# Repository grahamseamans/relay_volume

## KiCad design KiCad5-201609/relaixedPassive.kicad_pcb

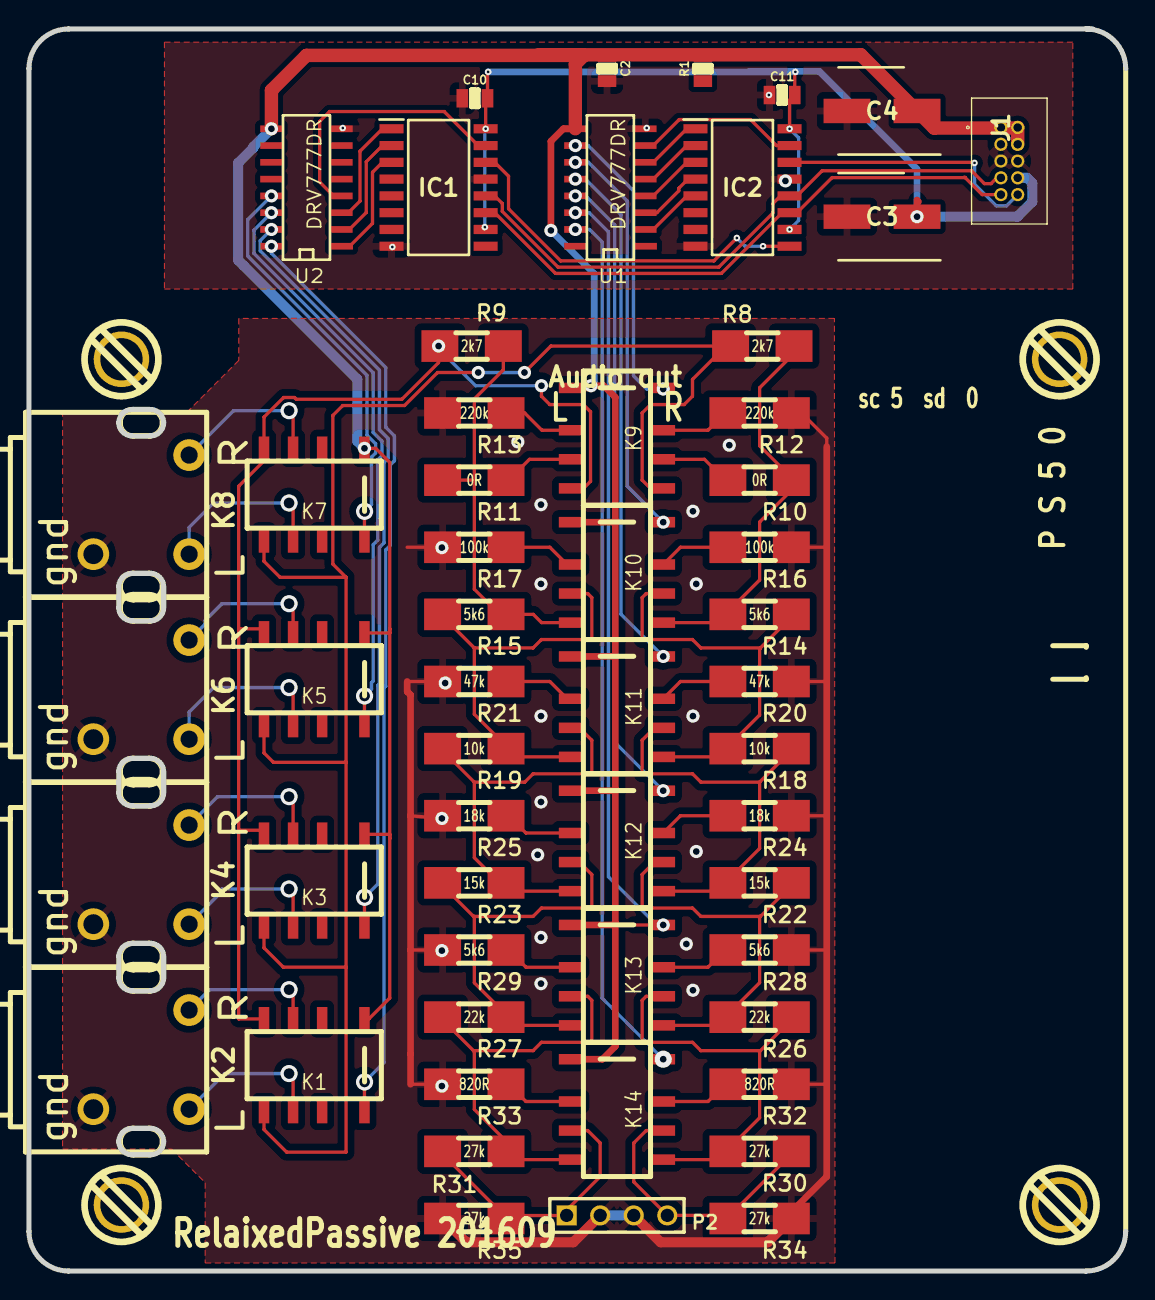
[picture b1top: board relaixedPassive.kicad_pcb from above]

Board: 2 copper layers, 83.0 x 94.0 mm, 58 parts (0 on the bottom side), 64 nets.

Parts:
1PIN, 1PIN#2, 1PIN#3, 1PIN#4: P***; screw-3mm
C2: 10uF; R0805
C3, C4: VZL221M1CTR-0607; CAPAE660X800N
C10, C11: 0.1uf; R0805
IC1, IC2: SN74HC595NSR; SOIC127P780X200-16N
J1: TFM-105-01-F-D; TFM-105-XX-YYY-D
K1, K3, K5, K7: RELAY_G6K_AB; G6K-2F-Y
K2, K4, K6, K8: CINCH-DUAL; switchcraft-dualcinch
K9, K10, K11, K12, K13, K14: RELAY_G6K; G6K-2F-Y
P2: audioOut; PIN_ARRAY_4x1
R1: 1k; R0805
R8, R9: 2k7; MMB0207-1210
R10, R11: 0R; MMB0207-1210
R12, R13: 220k; MMB0207-1210
R14, R15, R28, R29: 5k6; MMB0207-1210
R16, R17: 100k; MMB0207-1210
R18, R19: 10k; MMB0207-1210
R20, R21: 47k; MMB0207-1210
R22, R23: 15k; MMB0207-1210
R24, R25: 18k; MMB0207-1210
R26, R27: 22k; MMB0207-1210
R30, R31, R34, R35: 27k; MMB0207-1210
R32, R33: 820R; MMB0207-1210
U1, U2: DRV777DR; SO16E

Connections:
+3.3V: C3.1, C10.2, C11.2, IC1.10 (~SRCLR), IC1.16 (VCC), IC2.10 (~SRCLR), IC2.16 (VCC), J1.8
+5V: C2.1, C4.1, J1.1, J1.2, J1.4, K1.1, K3.1, K5.1, K7.1, K9.1, K10.1, K11.1, K12.1, K13.1, K14.1, R1.2, U1.9 (COM), U2.9 (COM)
AGND: K2.3 (GL), K4.3 (GL), K6.3 (GL), K8.3 (GL), P2.2, P2.3, R12.1, R13.1, R16.1, R17.1, R20.1, R21.1, R24.1, R25.1, R28.1, R29.1, R32.1, R33.1, R34.2, R35.2
CH1: K1.8, U2.16 (O1)
CH2: K3.8, U2.15 (O2)
CH3: K5.8, U2.14 (O3)
CH4: K7.8, U2.13 (O4)
DGND: C2.2, C3.2, C4.2, C10.1, C11.1, IC1.8 (GND), IC1.13 (~OE), IC2.8 (GND), IC2.13 (~OE), J1.3, J1.5, J1.6, U1.8 (GND), U2.8 (GND)
unnamed: IC1.14 (SER), IC2.9 (QH')
unnamed: K1.4, K3.4, K5.4, K7.4, K9.4, R9.2
unnamed: K1.5, K3.5, K5.5, K7.5, K9.5, R8.2
unnamed: K1.6, K2.2 (L)
unnamed: K1.3, K2.1 (R)
unnamed: K3.6, K4.2 (L)
unnamed: K3.3, K4.1 (R)
unnamed: K5.6, K6.2 (L)
unnamed: K5.3, K6.1 (R)
unnamed: K7.6, K8.2 (L)
unnamed: K7.3, K8.1 (R)
unnamed: K9.2, R13.2
unnamed: K9.3, R11.2
unnamed: K9.6, R10.2
unnamed: K9.7, R12.2
unnamed: K10.2, R17.2
unnamed: K10.3, K11.4, R15.1, R19.2
unnamed: K10.4, R9.1, R11.1, R15.2
unnamed: K10.5, R8.1, R10.1, R14.2
unnamed: K10.6, K11.5, R14.1, R18.2
unnamed: K10.7, R16.2
unnamed: K11.2, R21.2
unnamed: K11.3, K12.4, R19.1, R23.2
unnamed: K11.6, K12.5, R18.1, R22.2
unnamed: K11.7, R20.2
unnamed: K12.2, R25.2
unnamed: K12.3, K13.4, R23.1, R27.2
unnamed: K12.6, K13.5, R22.1, R26.2
unnamed: K12.7, R24.2
unnamed: K13.2, R29.2
unnamed: K13.3, K14.4, R27.1, R31.2
unnamed: K13.6, K14.5, R26.1, R30.2
unnamed: K13.7, R28.2
unnamed: K14.2, R33.2
unnamed: K14.7, R32.2
unnamed: K14.3, P2.1, R31.1, R35.1
unnamed: K14.6, P2.4, R30.1, R34.1
RCLK1: IC1.12 (RCLK), IC2.12 (RCLK), J1.7
SER1: IC2.14 (SER), J1.10
SRCLK1: IC1.11 (SRCLK), IC2.11 (SRCLK), J1.9
VL0: K9.8, U1.10 (O7)
VL0c: IC2.15 (QA), U1.7 (I7)
VL1: K10.8, U1.11 (O6)
VL1c: IC2.1 (QB), U1.6 (I6)
VL2: K11.8, U1.12 (O5)
VL2c: IC2.2 (QC), U1.5 (I5)
VL3: K12.8, U1.13 (O4)
VL3c: IC2.3 (QD), U1.4 (I4)
VL4: K13.8, U1.14 (O3)
VL4c: IC2.4 (QE), U1.3 (I3)
VL5: K14.8, U1.15 (O2)
VL5c: IC2.5 (QF), U1.2 (I2)
contCH1: IC1.15 (QA), U2.4 (I4)
contCH2: IC1.1 (QB), U2.3 (I3)
contCH3: IC1.2 (QC), U2.2 (I2)
contCH4: IC1.3 (QD), U2.1 (I1)

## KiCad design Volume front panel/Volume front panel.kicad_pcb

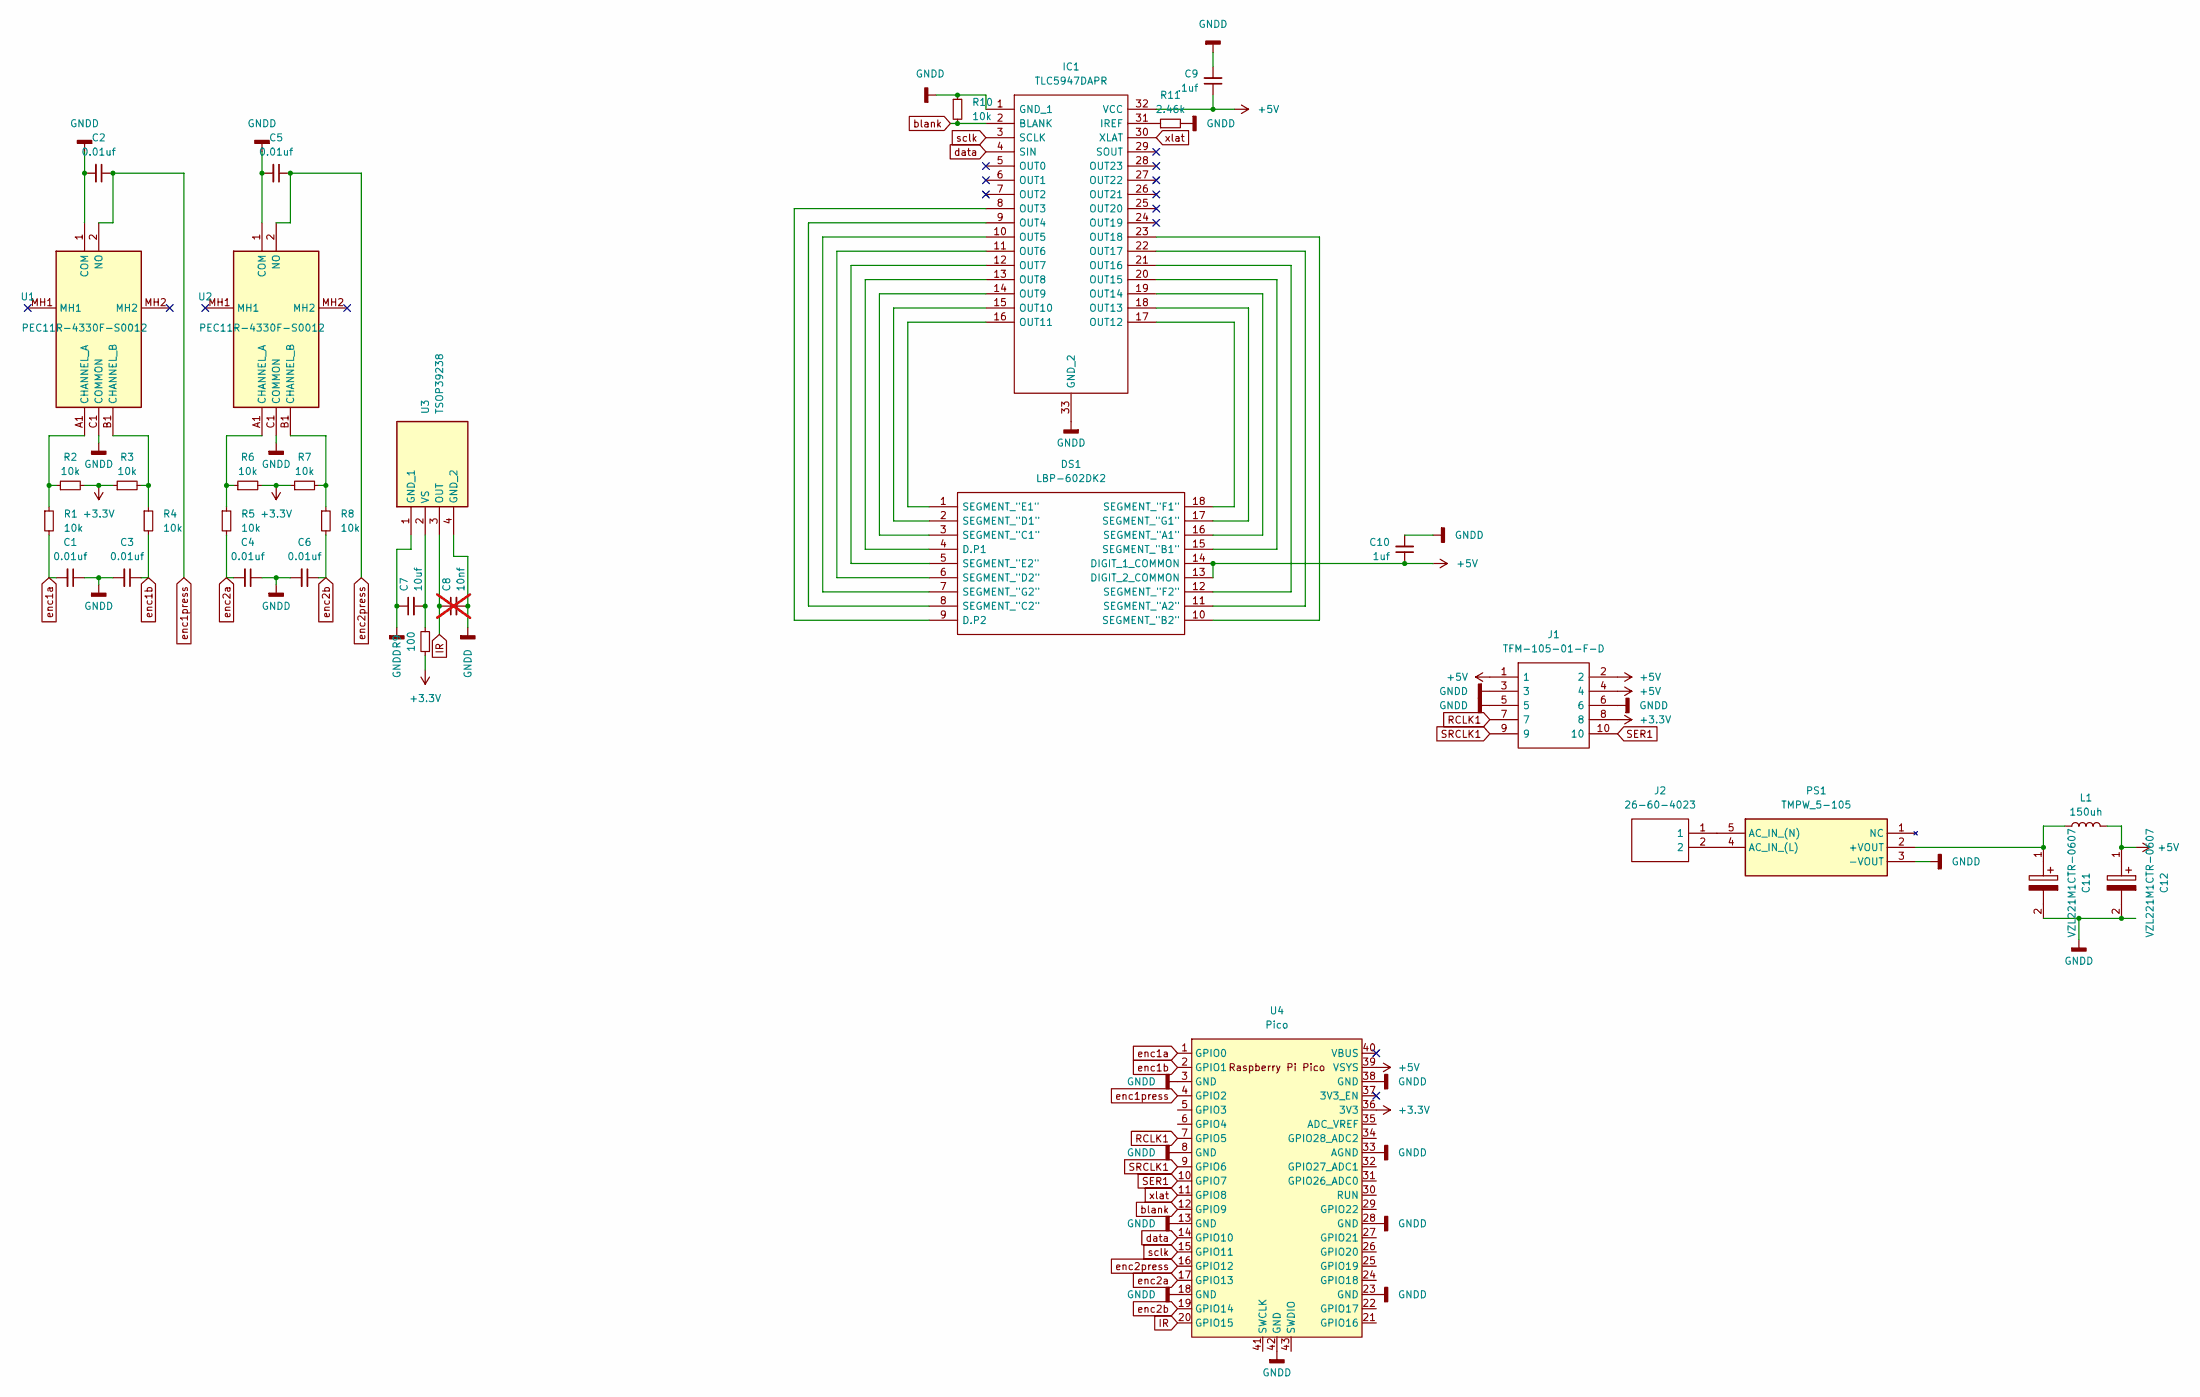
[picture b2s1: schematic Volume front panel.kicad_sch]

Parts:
C1, C2, C3, C4, C5, C6: 0.01uf; C_1206_3216Metric
C7: 10uf; C_1206_3216Metric
C8: 10nf; C_1206_3216Metric; not fitted
C9: .1uf; C_1206_3216Metric
C10: 1uf; C_1206_3216Metric
C11, C12: VZL221M1CTR-0607; CAPAE660X800N; Mouser Part Number 140-VZL221M1CTR-0607
DS1: LBP-602DK2; DIPS1524W50P254L2500H830Q18N; Mouser Part Number 755-LBP-602DK2
IC1: TLC5947DAPR; SOP65P810X120-33N; Mouser Part Number 595-TLC5947DAPR
J1: TFM-105-01-F-D; TFM-105-XX-YYY-D; Mouser Part Number 200-TFM10501FD
J2: 26-60-4023; 26604023; Mouser Part Number 538-26-60-4023
L1: 150uh; L_Coilcraft_XAL6060-XXX
PS1: TMPW_5-105; TMPW5112; Mouser Part Number 495-TMPW5-105
R1, R2, R3, R4, R5, R6, R7, R8, R10: 10k; R_1206_3216Metric
R9: 100; R_1206_3216Metric
R11: 2.46k; R_1206_3216Metric
U1, U2: PEC11R-4330F-S0012; PEC11R4330FS0012; Mouser Part Number 652-PEC11R4330FS0012
U3: TSOP39238; Mouser Part Number 78-TSOP39238
U4: Pico; RPi_Pico_SMD_TH

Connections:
+3.3V: J1.8, R2.2, R3.1, R6.2, R7.1, R9.1, U4.36 (3V3)
+5V: C9.1, C10.1, C12.1, DS1.13 (DIGIT_2_COMMON), DS1.14 (DIGIT_1_COMMON), IC1.32 (VCC), J1.1, J1.2, J1.4, L1.2, U4.39 (VSYS)
GNDD: C1.1, C2.2, C3.2, C4.1, C5.2, C6.2, C7.1, C8.2, C9.2, C10.2, C11.2, C12.2, IC1.1 (GND_1), IC1.33 (GND_2), J1.3, J1.5, J1.6, PS1.3 (-VOUT), R10.1, R11.2, U1.1 (COM), U1.C1 (COMMON), U2.1 (COM), U2.C1 (COMMON), U3.1 (GND_1), U3.4 (GND_2), U4.3 (GND), U4.8 (GND), U4.13 (GND), U4.18 (GND), U4.23 (GND), U4.28 (GND), U4.33 (AGND), U4.38 (GND), U4.42 (GND)
IR: C8.1, U3.3 (OUT), U4.20 (GPIO15)
unnamed: DS1.4 (D.P1), IC1.13 (OUT8)
unnamed: DS1.9 (D.P2), IC1.8 (OUT3)
unnamed: DS1.16 (SEGMENT_"A1"), IC1.19 (OUT14)
unnamed: DS1.11 (SEGMENT_"A2"), IC1.22 (OUT17)
unnamed: DS1.15 (SEGMENT_"B1"), IC1.20 (OUT15)
unnamed: DS1.10 (SEGMENT_"B2"), IC1.23 (OUT18)
unnamed: DS1.3 (SEGMENT_"C1"), IC1.14 (OUT9)
unnamed: DS1.8 (SEGMENT_"C2"), IC1.9 (OUT4)
unnamed: DS1.2 (SEGMENT_"D1"), IC1.15 (OUT10)
unnamed: DS1.6 (SEGMENT_"D2"), IC1.11 (OUT6)
unnamed: DS1.1 (SEGMENT_"E1"), IC1.16 (OUT11)
unnamed: DS1.5 (SEGMENT_"E2"), IC1.12 (OUT7)
unnamed: DS1.18 (SEGMENT_"F1"), IC1.17 (OUT12)
unnamed: DS1.12 (SEGMENT_"F2"), IC1.21 (OUT16)
unnamed: DS1.17 (SEGMENT_"G1"), IC1.18 (OUT13)
unnamed: DS1.7 (SEGMENT_"G2"), IC1.10 (OUT5)
unnamed: IC1.31 (IREF), R11.1
unnamed: C11.1, L1.1, PS1.2 (+VOUT)
unnamed: J2.2, PS1.4 (AC_IN_(L))
unnamed: J2.1, PS1.5 (AC_IN_(N))
unnamed: R1.1, R2.1, U1.A1 (CHANNEL_A)
unnamed: R3.2, R4.1, U1.B1 (CHANNEL_B)
unnamed: R5.1, R6.1, U2.A1 (CHANNEL_A)
unnamed: R7.2, R8.1, U2.B1 (CHANNEL_B)
unnamed: C7.2, R9.2, U3.2 (VS)
RCLK1: J1.7, U4.7 (GPIO5)
SER1: J1.10, U4.10 (GPIO7)
SRCLK1: J1.9, U4.9 (GPIO6)
blank: IC1.2 (BLANK), R10.2, U4.12 (GPIO9)
data: IC1.4 (SIN), U4.14 (GPIO10)
enc1a: C1.2, R1.2, U4.1 (GPIO0)
enc1b: C3.1, R4.2, U4.2 (GPIO1)
enc1press: C2.1, U1.2 (NO), U4.4 (GPIO2)
enc2a: C4.2, R5.2, U4.17 (GPIO13)
enc2b: C6.1, R8.2, U4.19 (GPIO14)
enc2press: C5.1, U2.2 (NO), U4.16 (GPIO12)
sclk: IC1.3 (SCLK), U4.15 (GPIO11)
xlat: IC1.30 (XLAT), U4.11 (GPIO8)

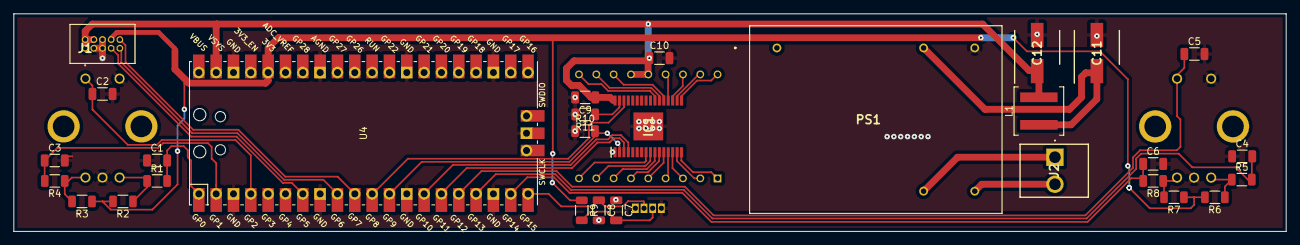
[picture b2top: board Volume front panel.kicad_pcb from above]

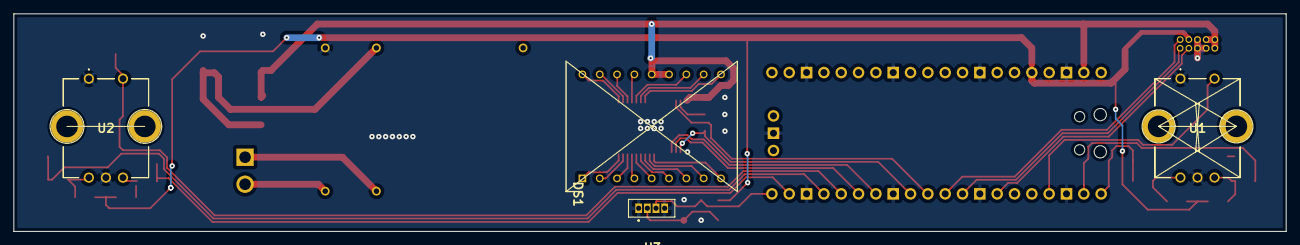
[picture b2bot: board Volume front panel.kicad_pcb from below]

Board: 2 copper layers, 186.5 x 31.9 mm, 33 parts (4 on the bottom side), 42 nets.

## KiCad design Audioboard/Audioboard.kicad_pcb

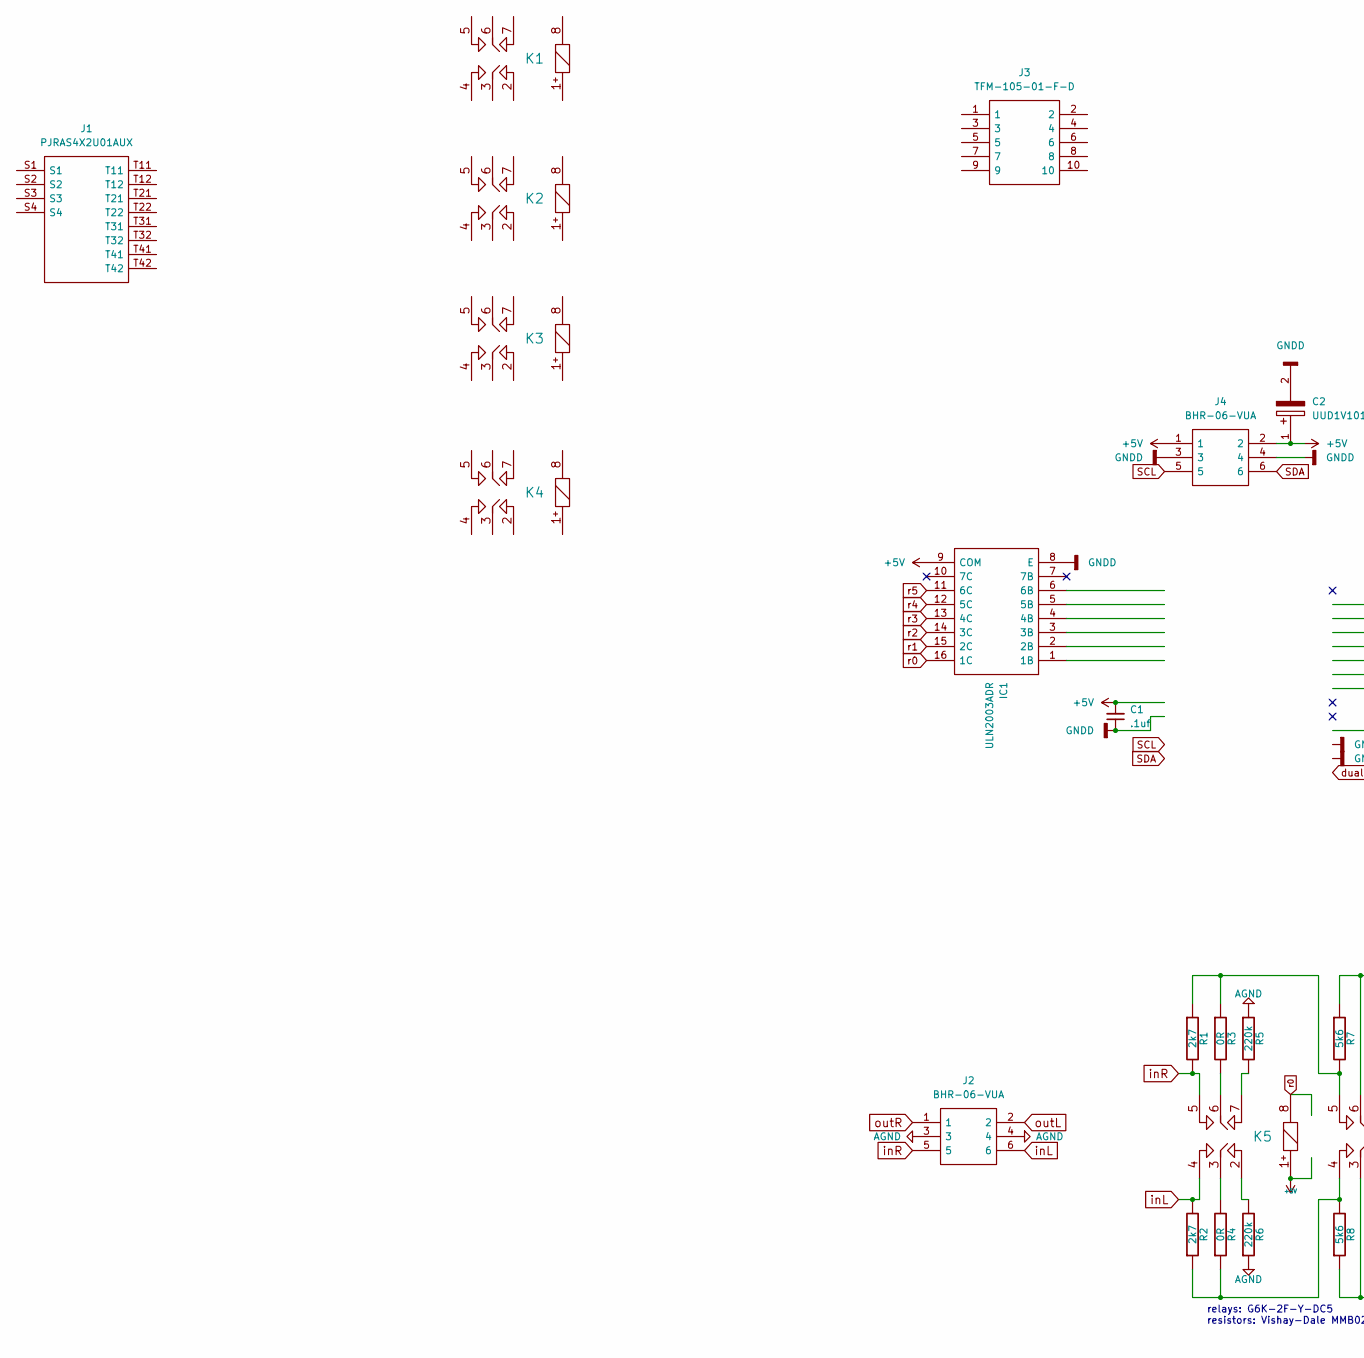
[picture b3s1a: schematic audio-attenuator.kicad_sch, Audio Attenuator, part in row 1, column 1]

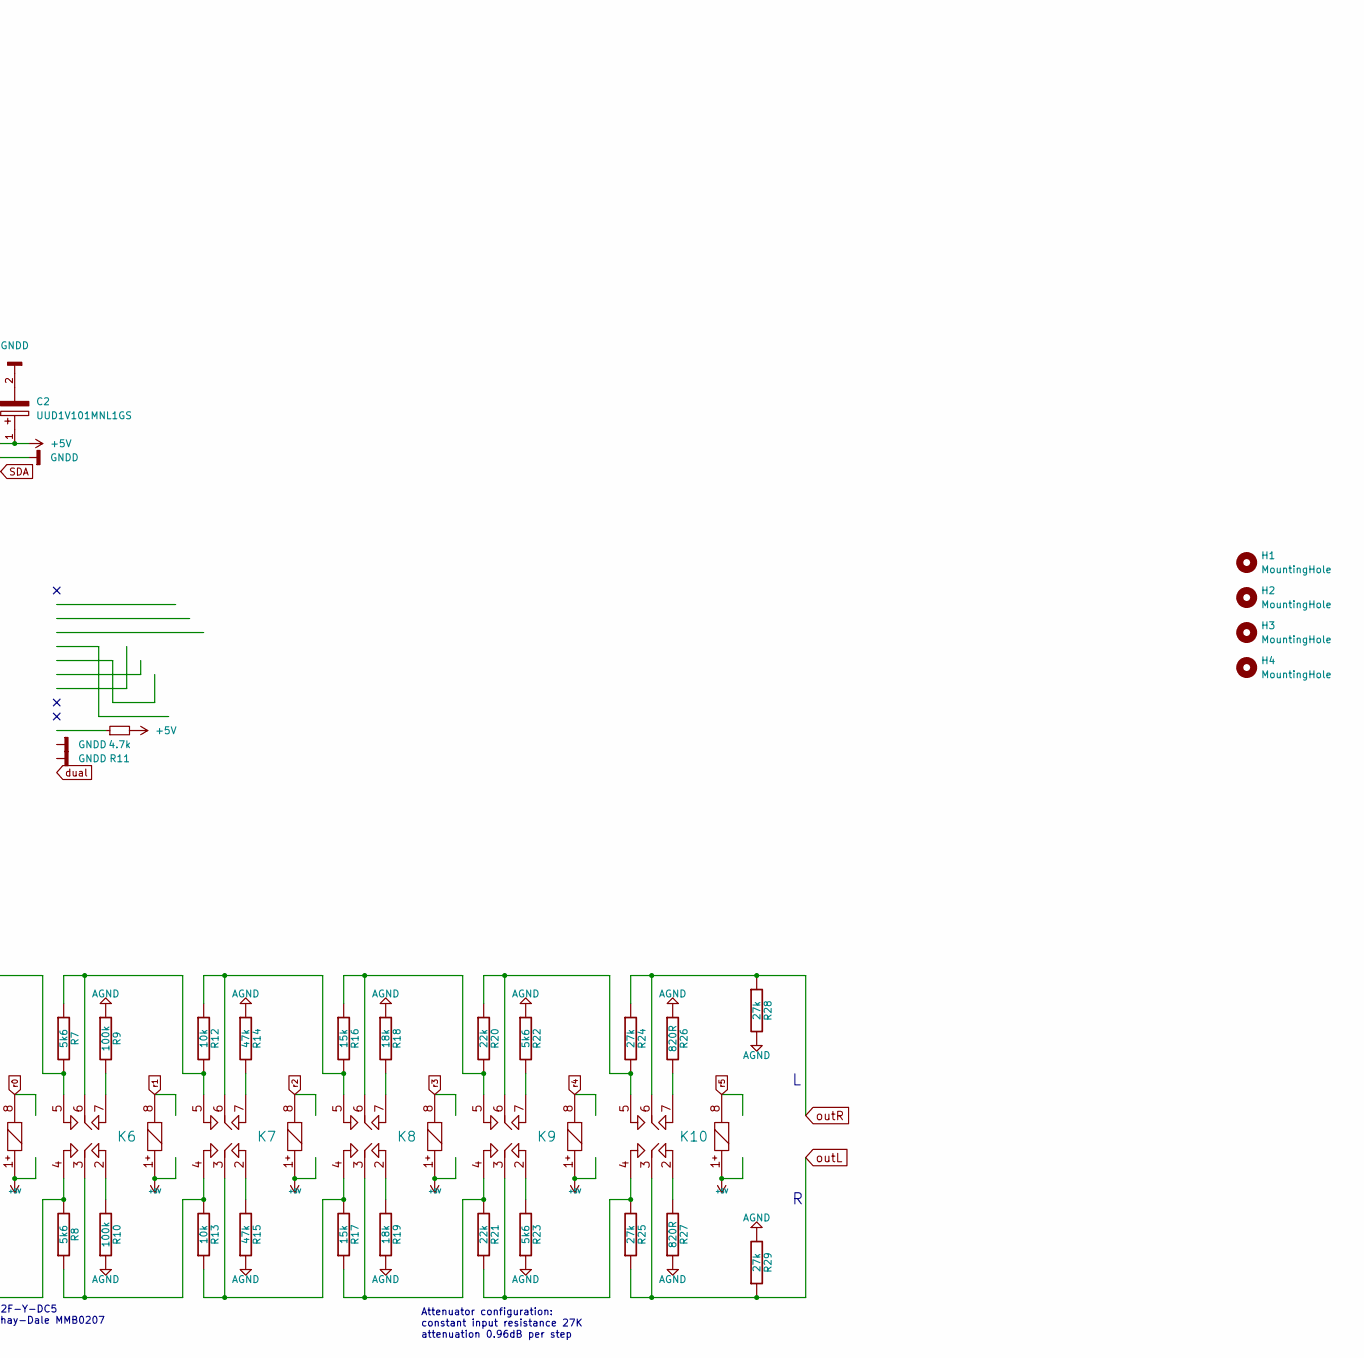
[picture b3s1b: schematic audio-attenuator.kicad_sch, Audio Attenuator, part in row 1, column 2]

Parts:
C1: .1uf; C_1206_3216Metric
C2: UUD1V101MNL1GS; CAPAE830X1050N; Mouser Part Number 647-UUD1V101MNL
H1, H2, H3, H4: MountingHole; MountingHole_3.2mm_M3_ISO7380
IC1: ULN2003ADR; SOIC127P600X175-16N; Mouser Part Number 595-ULN2003ADR
J1: PJRAS4X2U01AUX; Mouser Part Number 502-PJRAS4X2U01AUX
J2, J4: BHR-06-VUA; SHDR6W64P254_2X3_1522X880X920P; Mouser Part Number 737-BHR-06-VUA
J3: TFM-105-01-F-D; TFM-105-XX-YYY-D; Mouser Part Number 200-TFM10501FD
K1, K2, K3, K4, K5, K6, K7, K8, K9, K10: RELAY_G6K; G6K-2F-Y
R1, R2: 2k7; R_MELF_MMB-0207
R3, R4: 0R; R_MELF_MMB-0207
R5, R6: 220k; R_MELF_MMB-0207
R7, R8, R22, R23: 5k6; R_MELF_MMB-0207
R9, R10: 100k; R_MELF_MMB-0207
R11: 4.7k; R_1206_3216Metric
R12, R13: 10k; R_MELF_MMB-0207
R14, R15: 47k; R_MELF_MMB-0207
R16, R17: 15k; R_MELF_MMB-0207
R18, R19: 18k; R_MELF_MMB-0207
R20, R21: 22k; R_MELF_MMB-0207
R24, R25, R28, R29: 27k; R_MELF_MMB-0207
R26, R27: 820R; R_MELF_MMB-0207

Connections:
+5V: C1.2, C2.1, IC1.9 (COM), J4.1, J4.2, K5.1, K6.1, K7.1, K8.1, K9.1, K10.1, R11.2
AGND: J2.3, J2.4, R5.1, R6.1, R9.1, R10.1, R14.1, R15.1, R18.1, R19.1, R22.1, R23.1, R26.1, R27.1, R28.2, R29.2
GNDD: C1.1, C2.2, IC1.8 (E), J4.3, J4.4
unnamed: K5.2, R6.2
unnamed: K5.3, R4.2
unnamed: K5.6, R3.2
unnamed: K5.7, R5.2
unnamed: K6.2, R10.2
unnamed: K6.3, K7.4, R8.1, R13.2
unnamed: K6.4, R2.1, R4.1, R8.2
unnamed: K6.5, R1.1, R3.1, R7.2
unnamed: K6.6, K7.5, R7.1, R12.2
unnamed: K6.7, R9.2
unnamed: K7.2, R15.2
unnamed: K7.3, K8.4, R13.1, R17.2
unnamed: K7.6, K8.5, R12.1, R16.2
unnamed: K7.7, R14.2
unnamed: K8.2, R19.2
unnamed: K8.3, K9.4, R17.1, R21.2
unnamed: K8.6, K9.5, R16.1, R20.2
unnamed: K8.7, R18.2
unnamed: K9.2, R23.2
unnamed: K9.7, R22.2
unnamed: K10.2, R27.2
unnamed: K9.3, K10.4, R21.1, R25.2
unnamed: K9.6, K10.5, R20.1, R24.2
unnamed: K10.7, R26.2
SCL: J4.5
SDA: J4.6
inL: J2.6, K5.4, R2.2
inR: J2.5, K5.5, R1.2
outL: J2.2, K10.3, R25.1, R29.1
outR: J2.1, K10.6, R24.1, R28.1
r0: IC1.16 (1C), K5.8
r1: IC1.15 (2C), K6.8
r2: IC1.14 (3C), K7.8
r3: IC1.13 (4C), K8.8
r4: IC1.12 (5C), K9.8
r5: IC1.11 (6C), K10.8

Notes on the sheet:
relays: G6K-2F-Y-DC5 resistors: Vishay-Dale MMB0207
Attenuator configuration: constant input resistance 27K attenuation 0.96dB per step

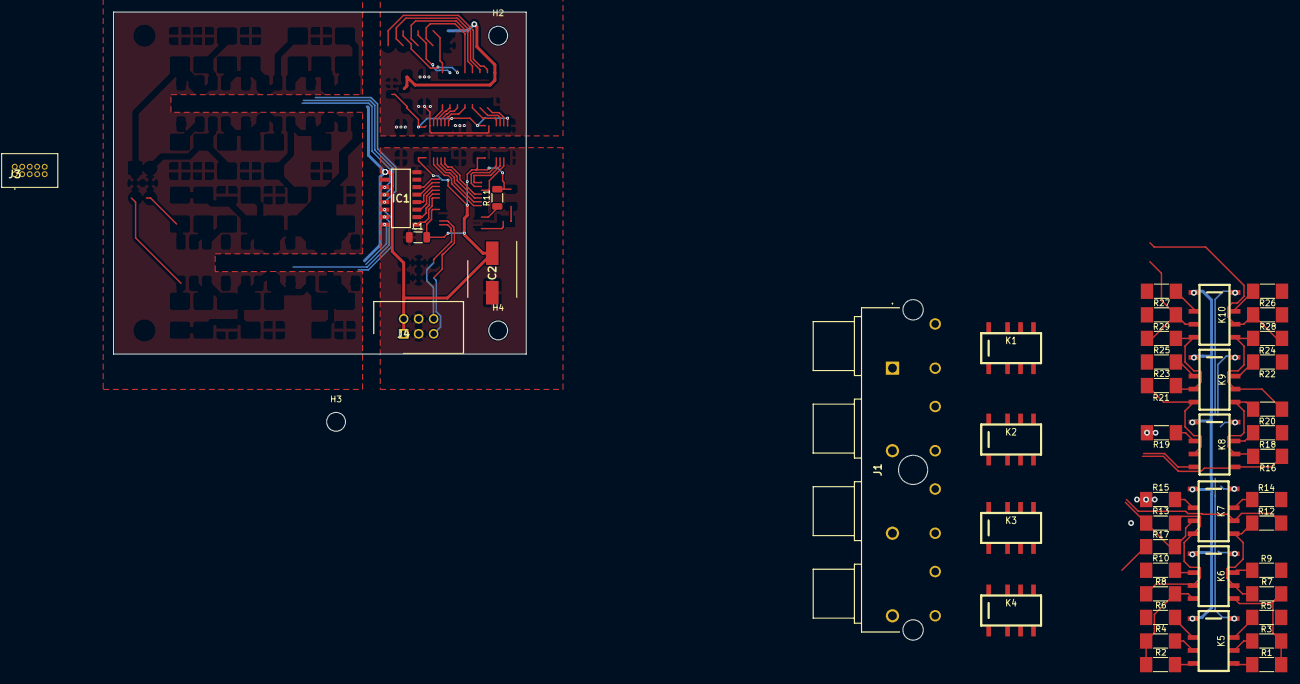
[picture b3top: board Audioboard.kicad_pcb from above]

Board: 2 copper layers, 70.0 x 58.0 mm, 49 parts (0 on the bottom side), 37 nets.

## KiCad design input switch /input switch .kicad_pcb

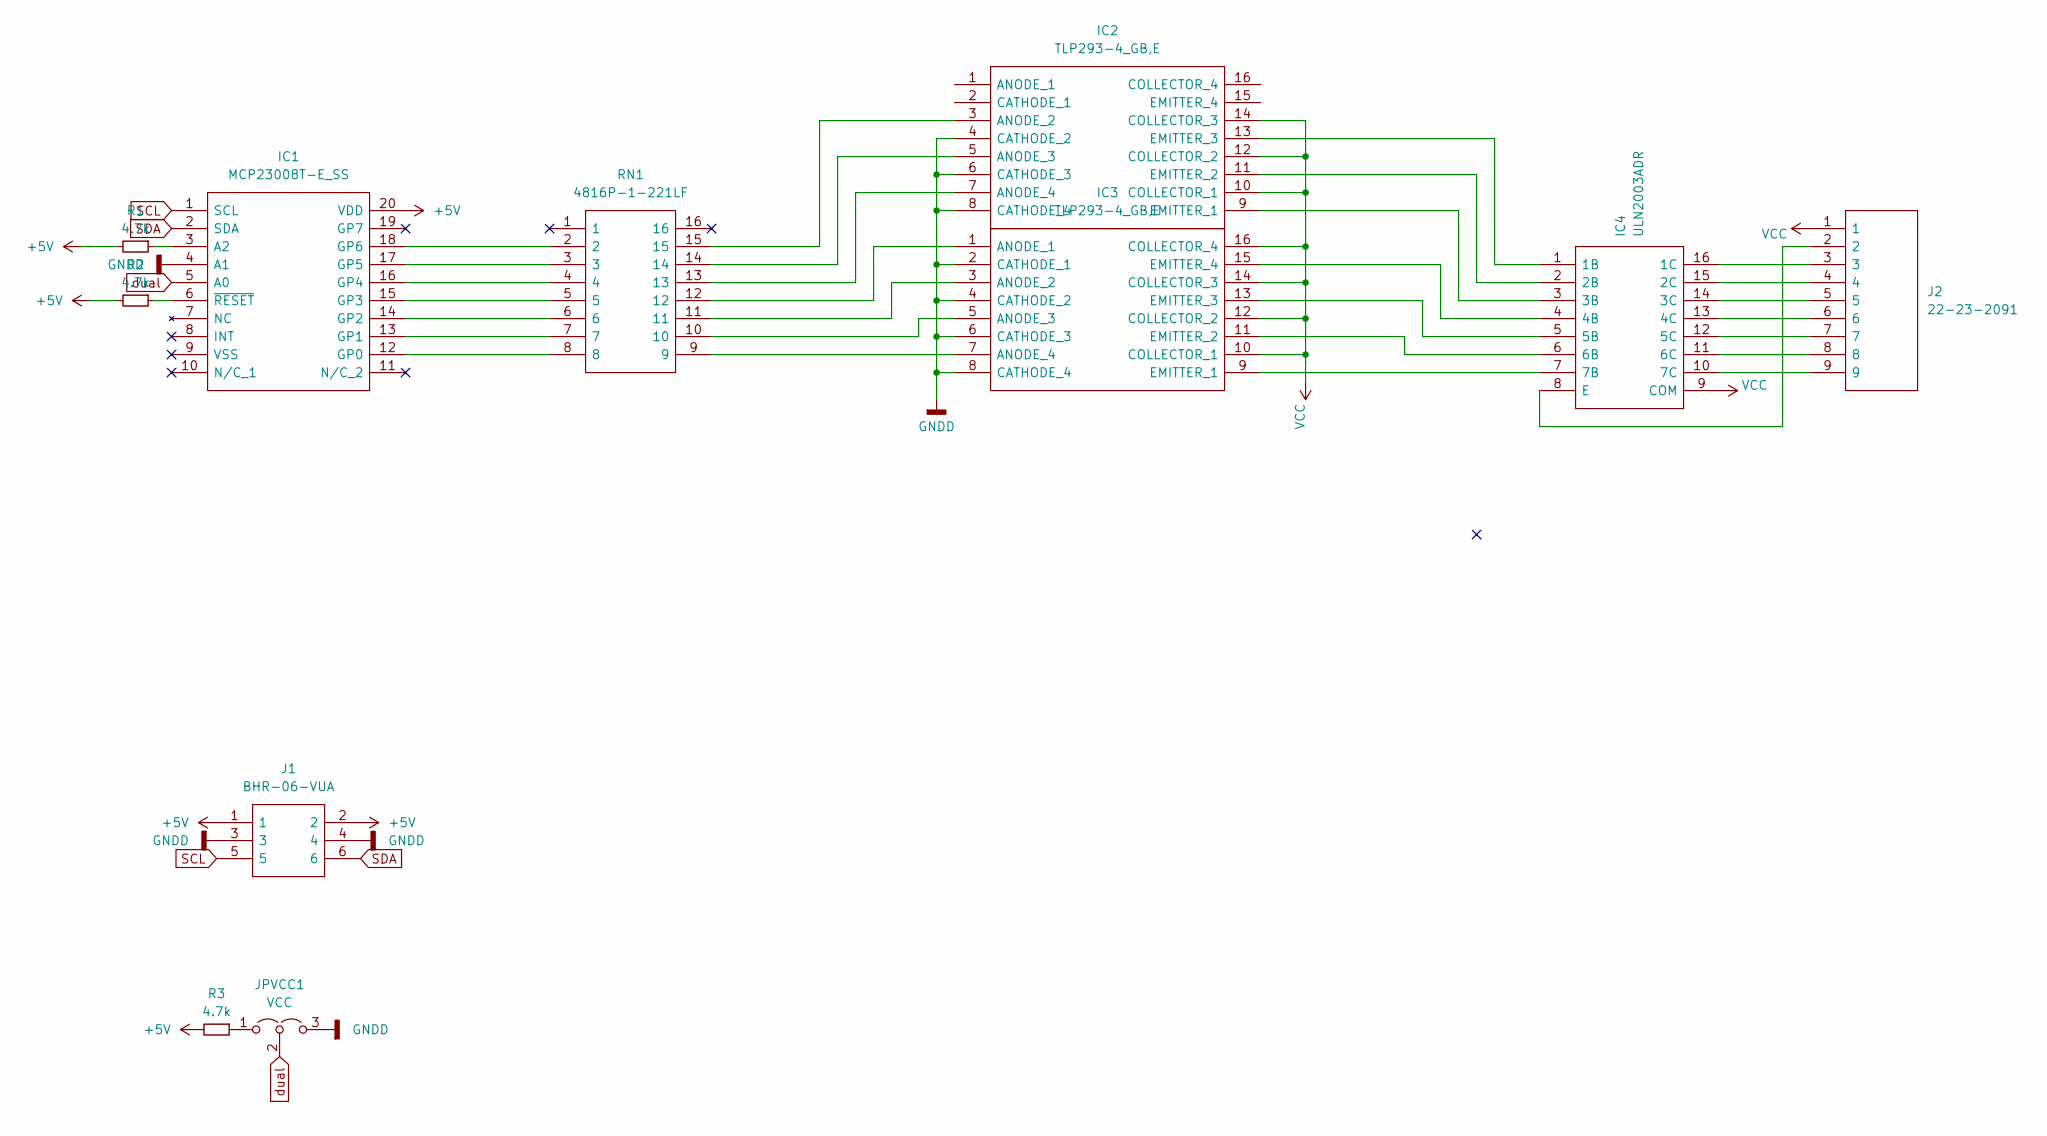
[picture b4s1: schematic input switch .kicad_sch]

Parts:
IC1: MCP23008T-E_SS; SOP65P780X200-20N; Mouser Part Number 579-MCP23008T-E/SS
IC2, IC3: TLP293-4_GB,E; SOIC127P700X220-16N; Mouser Part Number 757-TLP293-4GBE
IC4: ULN2003ADR; SOIC127P600X175-16N; Mouser Part Number 595-ULN2003ADR
J1: BHR-06-VUA; SHDR6W64P254_2X3_1522X880X920P; Mouser Part Number 737-BHR-06-VUA
J2: 22-23-2091; HDRV9W82P0X254_1X9_2271X635X1066P; Mouser Part Number 538-22-23-2091
JPVCC1: VCC; SolderJumper-3_P1.3mm_Open_Pad1.0x1.5mm
R1, R2, R3: 4.7k; R_1206_3216Metric
RN1: 4816P-1-221LF; SOIC127P762X240-16N; Mouser Part Number 652-4816P-1LF-220

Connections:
+5V: IC1.20 (VDD), J1.1, J1.2, R1.2, R2.2, R3.2
GNDD: IC1.4 (A1), IC2.4 (CATHODE_2), IC2.6 (CATHODE_3), IC2.8 (CATHODE_4), IC3.2 (CATHODE_1), IC3.4 (CATHODE_2), IC3.6 (CATHODE_3), IC3.8 (CATHODE_4), J1.3, J1.4, JPVCC1.3 (B)
unnamed: IC1.3 (A2), R1.1
unnamed: IC1.12 (GP0), RN1.8
unnamed: IC1.13 (GP1), RN1.7
unnamed: IC1.14 (GP2), RN1.6
unnamed: IC1.15 (GP3), RN1.5
unnamed: IC1.16 (GP4), RN1.4
unnamed: IC1.17 (GP5), RN1.3
unnamed: IC1.18 (GP6), RN1.2
unnamed: IC1.6 (~RESET), R2.1
unnamed: IC2.3 (ANODE_2), RN1.15
unnamed: IC2.5 (ANODE_3), RN1.14
unnamed: IC2.7 (ANODE_4), RN1.13
unnamed: IC2.9 (EMITTER_1), IC4.3 (3B)
unnamed: IC2.11 (EMITTER_2), IC4.2 (2B)
unnamed: IC2.13 (EMITTER_3), IC4.1 (1B)
unnamed: IC3.1 (ANODE_1), RN1.12
unnamed: IC3.3 (ANODE_2), RN1.11
unnamed: IC3.5 (ANODE_3), RN1.10
unnamed: IC3.7 (ANODE_4), RN1.9
unnamed: IC3.9 (EMITTER_1), IC4.7 (7B)
unnamed: IC3.11 (EMITTER_2), IC4.6 (6B)
unnamed: IC3.13 (EMITTER_3), IC4.5 (5B)
unnamed: IC3.15 (EMITTER_4), IC4.4 (4B)
unnamed: IC4.16 (1C), J2.3
unnamed: IC4.15 (2C), J2.4
unnamed: IC4.14 (3C), J2.5
unnamed: IC4.13 (4C), J2.6
unnamed: IC4.12 (5C), J2.7
unnamed: IC4.11 (6C), J2.8
unnamed: IC4.10 (7C), J2.9
unnamed: IC4.8 (E), J2.2
unnamed: JPVCC1.1 (A), R3.1
SCL: IC1.1 (SCL), J1.5
SDA: IC1.2 (SDA), J1.6
VCC: IC2.10 (COLLECTOR_1), IC2.12 (COLLECTOR_2), IC2.14 (COLLECTOR_3), IC3.10 (COLLECTOR_1), IC3.12 (COLLECTOR_2), IC3.14 (COLLECTOR_3), IC3.16 (COLLECTOR_4), IC4.9 (COM), J2.1
dual: IC1.5 (A0), JPVCC1.2 (C)

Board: 2 copper layers, 11 parts (0 on the bottom side), 38 nets, no tracks yet.

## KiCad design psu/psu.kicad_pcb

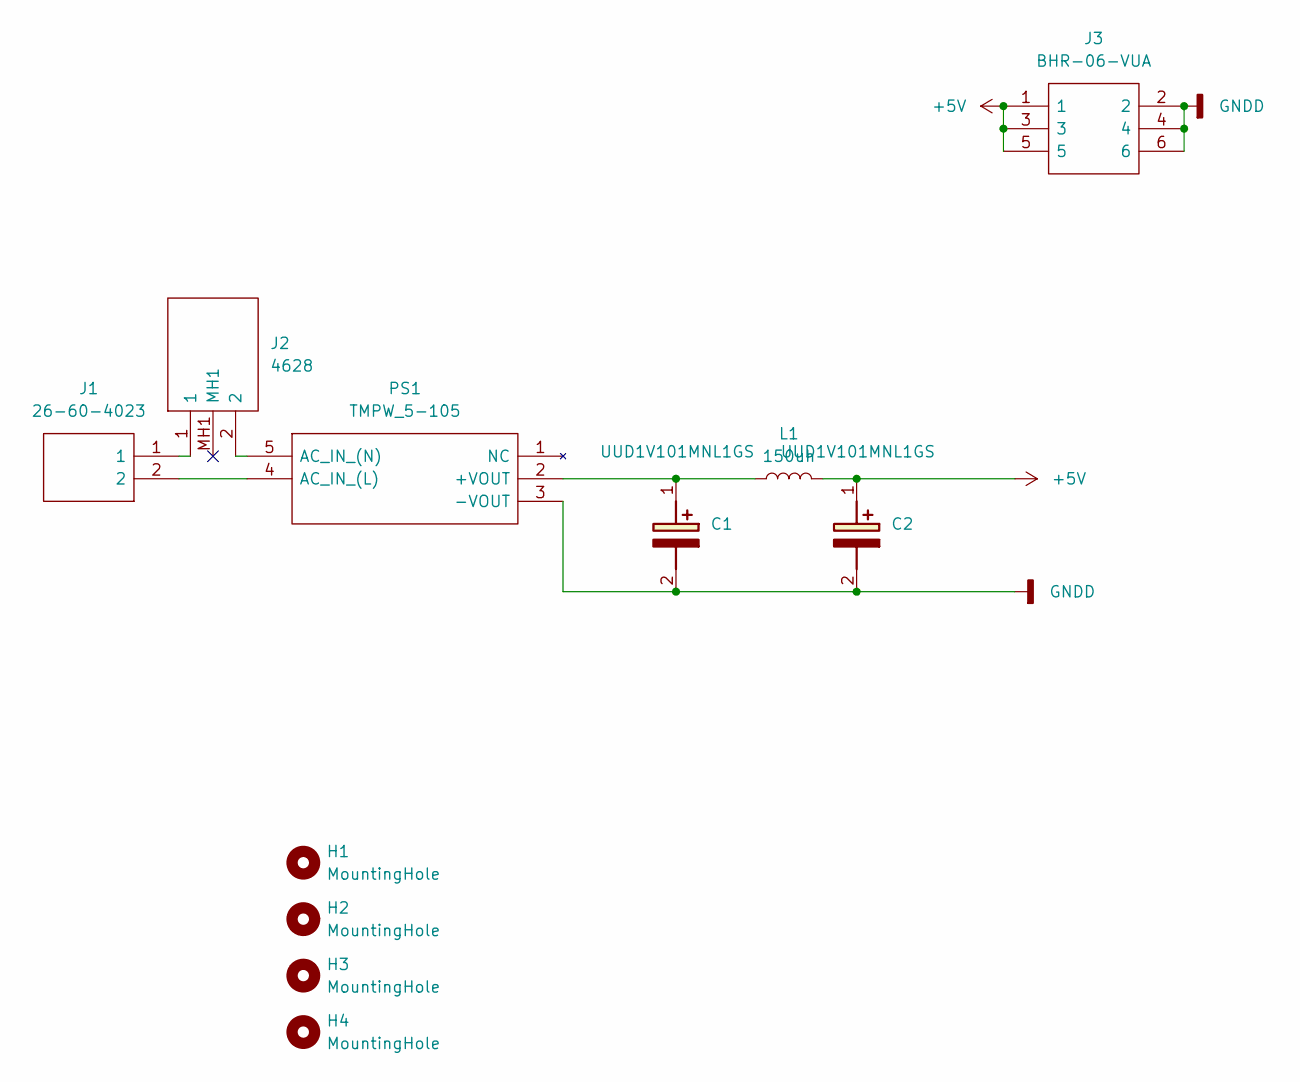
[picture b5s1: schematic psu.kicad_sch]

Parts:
C1, C2: UUD1V101MNL1GS; CAPAE830X1050N; Mouser Part Number 647-UUD1V101MNL
H1, H2, H3, H4: MountingHole; MountingHole_3.2mm_M3_ISO7380
J1: 26-60-4023; 26604023; Mouser Part Number 538-26-60-4023
J2: 4628; Mouser Part Number 534-4628
J3: BHR-06-VUA; SHDR6W64P254_2X3_1522X880X920P; Mouser Part Number 737-BHR-06-VUA
L1: 150uh; L_Bourns_SRR1260
PS1: TMPW_5-105; TMPW5112; Mouser Part Number 495-TMPW5-105

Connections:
+5V: C2.1 (+), J3.1, J3.3, J3.5, L1.2
GNDD: C1.2 (-), C2.2 (-), J3.2, J3.4, J3.6, PS1.3 (-VOUT)
unnamed: C1.1 (+), L1.1, PS1.2 (+VOUT)
unnamed: J1.1, J2.1
unnamed: J1.2, PS1.4 (AC_IN_(L))
unnamed: J2.2, PS1.5 (AC_IN_(N))

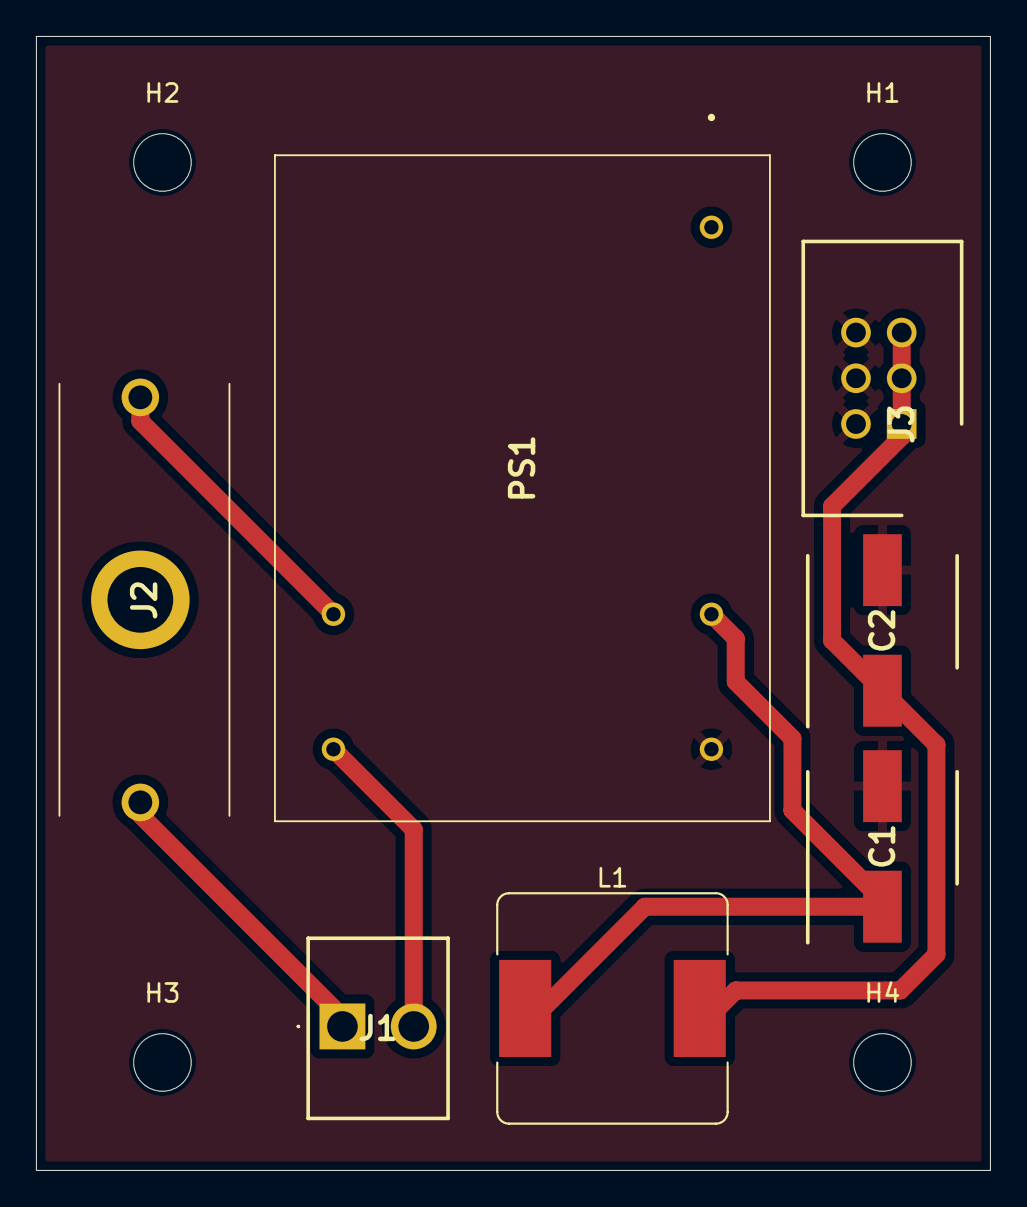
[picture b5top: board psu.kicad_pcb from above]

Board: 2 copper layers, 53.0 x 63.0 mm, 11 parts (0 on the bottom side), 6 nets.

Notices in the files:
Audioboard/Audioboard.kicad_pcb:
Copyright 2016
